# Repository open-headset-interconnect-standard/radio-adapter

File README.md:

# Open Source OHIS Radio Adapter(s?)
An open-source OHIS Radio Adapter.

As of 2024-07-17, this is a Work In Progress.

# Goals

1. Design a set of circuits that can be used to build OHIS compliant radio adapters.
2. Designs should be as simple as possible, but no simpler.
3. When laying out boards, keep as many parts through-hole as possible for ease of assembly.
4. There are two types of designs here:
    1. **General:** Has all the circuits required to work with any radio, that needs to be configured.
    2. **Radio Specific:** Trades Configurability for Simplicity.  Make a simpler device for a specific radio.

# Directory Structure

All KiCAD projects are in their own subdirectories off the git root.  Where it makes sense to do so, an additional layer of subdirectory may be used to group several projects together more obviously.

`/Documentation/` and `/docs/` are reserved for documentation source, and documentation output, respectively.

Everything in `/docs/` will be published on github Pages.

## Icom, Yaesu, Kenwood

As of 2024-04-04, I (@SmittyHalibut, Mark Smith, N6MTS) have submitted three schematics (only!) for VERY SIMPLE radio controllers for the Big Three.  A few notes about these:

* **I HAVE NOT TESTED THEM!**  There's no guaranty that they'll work, or even that they won't blow up your radio.  (It most likely won't blow up your radio. Probably.  I think.  It might.  It shouldn't.  Yeah, probably not.  But there's no telling.)
    * If you find a better way to do any of this, please submit a Pull Request, or at least an Issue with your idea.
* **YOU HAVE TO VERIFY PINOUTS MATCH YOUR RADIO!**  I've selected pinouts for most modern versions of these radios, but while researching this, it becomes obvious that older radios were not so consistent, even within a given manufacturer.  (Yaesu seems to be the worst at this, but they all do it.)
    * See [EB3GKE's Mic Pinout Reference](Yaesu/EB3GKE Mic Pinout Reference.pdf), it collects a lot of pinout information.  **BUT THEY GET RJ45 PINOUTS WRONG**.  As far as I could see, all (only most?) of their RJ45 pictures number pins 1 through 8 backwards.  OHIS's schematics are absolutely correct (verified against TIA-568 documents), so if the pinout for your radio looks VERY DIFFERENT than OHIS's pinouts, try reversing the pin numbers and see if thats closer.
* As of 2024-04-04, I've only done the schematics, and even then it's little more than throwing notes down "on paper."  I tried to cover:
    * Connector pinouts (see above).
    * Any electrical circuits required (mostly converting from OHIS's electret level to dynamic level for radios that want dynamic.)

As of 2024-04-25, I (still @SmittyHalibut) laid out the boards described above and had them fabricated.

* **I STILL HAVE NOT TESTED THEM!**

As of 2024-07-17, I (still me) am chatting with @gx1400 about this.  I'm going to send him some of the boards I ordered back in April and he'll help me test.

As of 2024-12-03, I (STILL me) am sending hardware to @gx1400 and a few others for testing.  These tests are covering:

* Yaesu:
  * :check: RJ45 8p8c
  * :check: RJ14 6p6c
  * :green_square: GX16
* Icom:
  * :green_square: RJ45 8p8c
  * :check: GX16
* Kenwood:
  * :check: RJ45 8p8c
  * :check: GX16

If you can test Yaesu GX16 or Icom RJ45, please reach out to me.  @SmittyHalibut on github, or on Discord.

# Parts

Electrical components, in recommended order of assembly:
* 1x 2x2 pin header right angle
* 1x 2x4 pin header right angle
* 1x 1k axial resistor
* 1x 6.2k axial resistor
* 2x 100R axial resistors
* 2x 10uF
* 1x 1k pot
* 1x 5381 (RJ45 with LED) for OHIS socket

Mechanical components, same as User kit:
* 4x M3 6mm screw
* 4x M3 10mm screw
* 4x M3 14mm brass stand-off
* 4x M3 3mm ABS stand-off
* 5x .1" jumper

PCBs in this repo:
* 2x Top-bottom panels
* 1x Main board
* 1x Shim board

Radio Specific parts, in recommended order of assembly:
* 1x Radio Specific Board
* 1x 3.5mm TRRS "headphone/speaker" connector
* Microphone connector.  Either one of:
  * 5380 (RJ45 with no LED) or 5381 (with LED) if its easier, but the LEDs aren't used.
  * GX16 connector, and GX16 riser board

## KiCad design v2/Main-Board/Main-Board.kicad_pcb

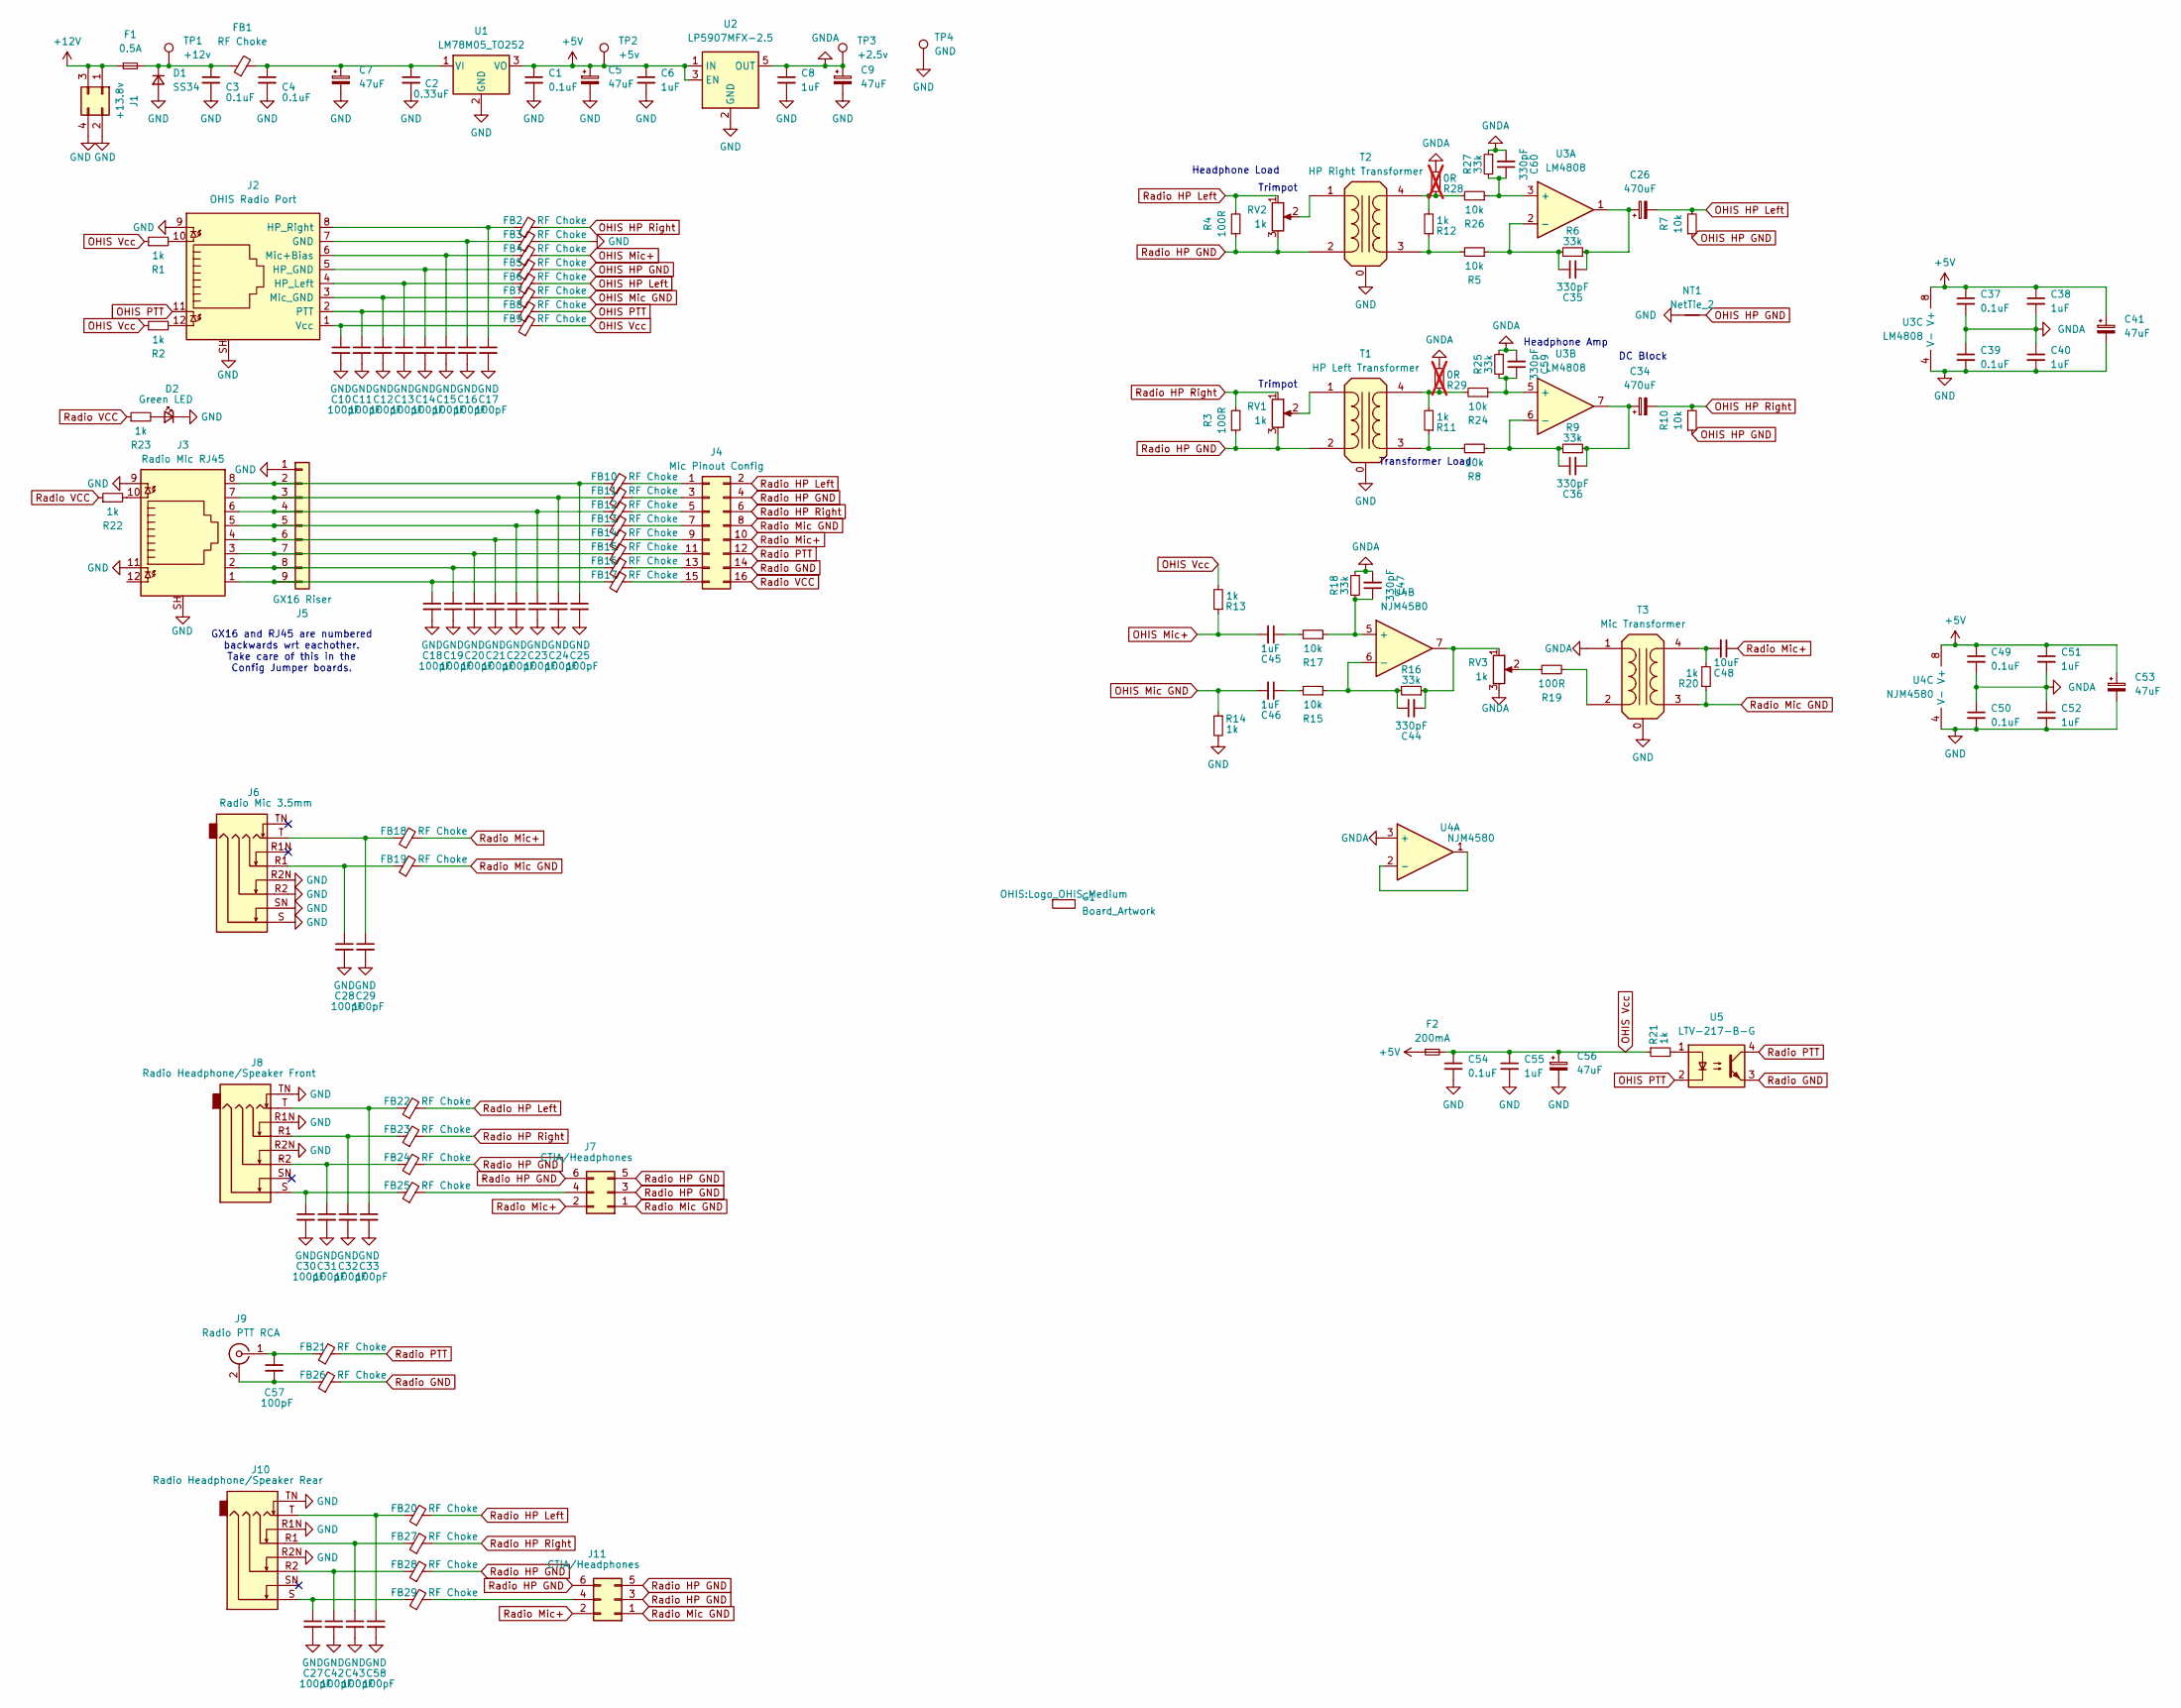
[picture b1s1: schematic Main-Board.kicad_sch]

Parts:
C1, C3, C4, C37, C39, C49, C50, C54: 0.1uF; C_0603_1608Metric; LCSC C14663
C2: 0.33uF; C_0603_1608Metric; LCSC C1615
C5, C9, C41, C53, C56: 47uF; C_0805_2012Metric; LCSC C16780
C6, C8, C38, C40, C45, C46, C51, C52, C55: 1uF; C_0603_1608Metric; LCSC C15849
C7: 47uF; CP_Elec_6.3x5.8; LCSC C401754
C10, C11, C12, C13, C14, C15, C16, C17, C18, C19, C20, C21, C22, C23, C24, C25, C27, C28, C29, C30, C31, C32, C33, C42, C43, C57, C58: 100pF; C_0603_1608Metric; LCSC C14858
C26, C34: 470uF; CP_Elec_6.3x7.7; LCSC C344072
C35, C36, C44, C47, C59, C60: 330pF; C_0603_1608Metric; LCSC C1664
C48: 10uF; C_0603_1608Metric; LCSC C19702
D1: SS34; D_SMA; LCSC C8678
D2: Green LED; LED_0805_2012Metric; LCSC C2297
F1: 0.5A; Fuse_1206_3216Metric; LCSC C720075
F2: 200mA; Fuse_0805_2012Metric; LCSC C516070
FB1, FB2, FB3, FB4, FB5, FB6, FB7, FB8, FB9, FB10, FB11, FB12, FB13, FB14, FB15, FB16, FB17, FB18, FB19, FB20, FB21, FB22, FB23, FB24, FB25, FB26, FB27, FB28, FB29: RF Choke; L_0805_2012Metric; LCSC C1017
G1: Board_Artwork; Logo_OHIS_Medium
J1: +13.8v; AndersonPP45-Dual
J2: OHIS Radio Port; Conn_RJ45_SMT_Amphenol-RJCSE-538X; LCSC C5384260
J3: Radio Mic RJ45; Conn_RJ45_SMT_Amphenol-RJCSE-538X; LCSC C5384260
J4: Mic Pinout Config; PinHeader_2x08_P2.54mm_Vertical_SMD; LCSC C32713288
J5: GX16 Riser; Conn_B2B-RA_2.54mm_9pin_Full-Slot
J6: Radio Mic 3.5mm; Conn_3.5mm-PJ-393-8_SMT-C668609; LCSC C668609
J7, J11: CTIA/Headphones; PinHeader_2x03_P2.54mm_Vertical_SMD; LCSC C32713283
J8: Radio Headphone/Speaker Front; Conn_3.5mm-PJ-393-8_SMT-C668609; LCSC C668609
J9: Radio PTT RCA; Conn_RCA_Kobiconn_156-009x-E
J10: Radio Headphone/Speaker Rear; Conn_3.5mm-PJ-393-8_SMT-C668609; LCSC C668609
NT1: NetTie_2; NetTie-2_SMD_Pad0.5mm
R1, R2, R11, R12, R13, R14, R20, R21, R22, R23: 1k; R_0603_1608Metric; LCSC C21190
R3, R4, R19: 100R; R_0603_1608Metric; LCSC C22775
R5, R7, R8, R10, R15, R17, R24, R26: 10k; R_0603_1608Metric; LCSC C25804
R6, R9, R16, R18, R25, R27: 33k; R_0603_1608Metric; LCSC C4216
R28, R29: 0R; R_0603_1608Metric; LCSC C21190; not fitted
RV1, RV2, RV3: 1k; Potentiometer_Bourns_3314J_Vertical; LCSC C124640
T1: HP Left Transformer; Transformer_ED8_4-Lead_10.5x8mm_P5mm; LCSC C840532
T2: HP Right Transformer; Transformer_ED8_4-Lead_10.5x8mm_P5mm; LCSC C840532
T3: Mic Transformer; Transformer_ED8_4-Lead_10.5x8mm_P5mm; LCSC C840532
TP1: +12v; TestPoint_THTPad_D1.5mm_Drill0.7mm
TP2: +5v; TestPoint_THTPad_D1.5mm_Drill0.7mm
TP3: +2.5v; TestPoint_THTPad_D1.5mm_Drill0.7mm
TP4: GND; TestPoint_THTPad_D1.5mm_Drill0.7mm
U1: LM78M05_TO252; TO-252-2; LCSC C58069
U2: LP5907MFX-2.5; SOT-23-5; LCSC C165132
U3: LM4808; SOP-8_3.76x4.96mm_P1.27mm; LCSC C910863
U4: NJM4580; SOP-8_3.76x4.96mm_P1.27mm; LCSC C3000516
U5: LTV-217-B-G; SO-4_4.4x2.3mm_P1.27mm; LCSC C115450

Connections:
+5V: C1.1, C5.1, C6.1, C37.1, C38.1, C41.1, C49.1, C51.1, C53.1, F2.1, TP2.1, U1.3 (VO), U2.1 (IN), U2.3 (EN), U3.8 (V+), U4.8 (V+)
+12V: F1.1, J1.1, J1.3
GND: C1.2, C2.2, C3.2, C4.2, C5.2, C6.2, C7.2, C8.2, C9.2, C10.2, C11.2, C12.2, C13.2, C14.2, C15.2, C16.2, C17.2, C18.2, C19.2, C20.2, C21.2, C22.2, C23.2, C24.2, C25.2, C27.2, C28.2, C29.2, C30.2, C31.2, C32.2, C33.2, C39.2, C40.2, C41.2, C42.2, C43.2, C50.2, C52.2, C53.2, C54.2, C55.2, C56.2, C58.2, D1.2 (A), D2.1 (K), FB3.2, J1.2, J1.4, J2.9, J2.SH, J3.9, J3.11, J3.SH, J5.1, J6.R2, J6.R2N, J6.S, J6.SN, J8.R1N, J8.R2N, J8.TN, J10.R1N, J10.R2N, J10.TN, NT1.1, R14.2, T1.0, T2.0, T3.0, TP4.1, U1.2 (GND), U2.2 (GND), U3.4 (V-), U4.4 (V-)
GNDA: C8.1, C9.1, C37.2, C38.2, C39.1, C40.1, C47.2, C49.2, C50.1, C51.2, C52.1, C59.2, C60.2, R18.1, R25.1, R27.1, R28.2, R29.2, RV3.3, T3.1 (AA), TP3.1, U2.5 (OUT), U4.3 (+)
unnamed: C26.1, C35.2, R6.1, U3.1
unnamed: C27.1, FB29.1, J10.S
unnamed: C28.1, FB19.1, J6.R1
unnamed: C29.1, FB18.1, J6.T
unnamed: C30.1, FB25.1, J8.S
unnamed: C31.1, FB24.1, J8.R2
unnamed: C32.1, FB23.1, J8.R1
unnamed: C33.1, FB22.1, J8.T
unnamed: C34.1, C36.2, R9.1, U3.7
unnamed: C42.1, FB28.1, J10.R2
unnamed: C43.1, FB27.1, J10.R1
unnamed: C44.2, R16.1, RV3.1, U4.7
unnamed: C45.1, R17.2
unnamed: C46.1, R15.2
unnamed: C58.1, FB20.1, J10.T
unnamed: C3.1, D1.1 (K), F1.2, FB1.1, TP1.1
unnamed: D2.2 (A), R23.2
unnamed: C16.1, FB3.1, J2.7 (GND)
unnamed: C14.1, FB5.1, J2.5 (HP_GND)
unnamed: C13.1, FB6.1, J2.4 (HP_Left)
unnamed: C17.1, FB2.1, J2.8 (HP_Right)
unnamed: C15.1, FB4.1, J2.6 (Mic+Bias)
unnamed: C12.1, FB7.1, J2.3 (Mic_GND)
unnamed: C11.1, FB8.1, J2.2 (PTT)
unnamed: J2.10, R1.2
unnamed: J2.12, R2.2
unnamed: C10.1, FB9.1, J2.1 (Vcc)
unnamed: J3.10, R22.2
unnamed: FB10.2, J4.1
unnamed: FB11.2, J4.3
unnamed: FB12.2, J4.5
unnamed: FB13.2, J4.7
unnamed: FB14.2, J4.9
unnamed: FB15.2, J4.11
unnamed: FB16.2, J4.13
unnamed: FB17.2, J4.15
unnamed: C25.1, FB10.1, J3.8, J5.2
unnamed: C24.1, FB11.1, J3.7, J5.3
unnamed: C23.1, FB12.1, J3.6, J5.4
unnamed: C22.1, FB13.1, J3.5, J5.5
unnamed: C21.1, FB14.1, J3.4, J5.6
unnamed: C20.1, FB15.1, J3.3, J5.7
unnamed: C19.1, FB16.1, J3.2, J5.8
unnamed: C18.1, FB17.1, J3.1, J5.9
unnamed: FB25.2, J7.4
unnamed: C57.2, FB26.1, J9.2 (Ext)
unnamed: C57.1, FB21.1, J9.1 (In)
unnamed: FB29.2, J11.4
unnamed: R19.1, RV3.2
unnamed: R21.2, U5.1
unnamed: RV1.2, T1.1 (AA)
unnamed: R8.2, R11.1, T1.3 (SA)
unnamed: R11.2, R24.2, R29.1, T1.4 (SB)
unnamed: RV2.2, T2.1 (AA)
unnamed: R5.2, R12.1, T2.3 (SA)
unnamed: R12.2, R26.2, R28.1, T2.4 (SB)
unnamed: R19.2, T3.2 (AB)
unnamed: C48.2, R20.2, T3.4 (SB)
unnamed: C2.1, C4.1, C7.1, FB1.2, U1.1 (VI)
unnamed: C60.1, R26.1, R27.2, U3.3 (+)
unnamed: C35.1, R5.1, R6.2, U3.2 (-)
unnamed: C59.1, R24.1, R25.2, U3.5 (+)
unnamed: C36.1, R8.1, R9.2, U3.6 (-)
unnamed: U4.1, U4.2 (-)
unnamed: C47.1, R17.1, R18.2, U4.5 (+)
unnamed: C44.1, R15.1, R16.2, U4.6 (-)
OHIS HP GND: FB5.2, NT1.2, R7.1, R10.1
OHIS HP Left: C26.2, FB6.2, R7.2
OHIS HP Right: C34.2, FB2.2, R10.2
OHIS Mic GND: C46.2, FB7.2, R14.1
OHIS Mic+: C45.2, FB4.2, R13.1
OHIS PTT: FB8.2, J2.11, U5.2
OHIS Vcc: C54.1, C55.1, C56.1, F2.2, FB9.2, R1.1, R2.1, R13.2, R21.1
Radio GND: FB26.2, J4.14, U5.3
Radio HP GND: FB24.2, FB28.2, J4.4, J7.3, J7.5, J7.6, J11.3, J11.5, J11.6, R3.1, R4.1, RV1.3, RV2.3, T1.2 (AB), T2.2 (AB)
Radio HP Left: FB20.2, FB22.2, J4.2, R4.2, RV2.1
Radio HP Right: FB23.2, FB27.2, J4.6, R3.2, RV1.1
Radio Mic GND: FB19.2, J4.8, J7.1, J11.1, R20.1, T3.3 (SA)
Radio Mic+: C48.1, FB18.2, J4.10, J7.2, J11.2
Radio PTT: FB21.2, J4.12, U5.4
Radio VCC: J4.16, R22.1, R23.1

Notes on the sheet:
Trimpot
Headphone Load
Headphone Amp
DC Block
GX16 and RJ45 are numbered backwards wrt eachother. Take care of this in the Config Jumper boards.
Transformer Load

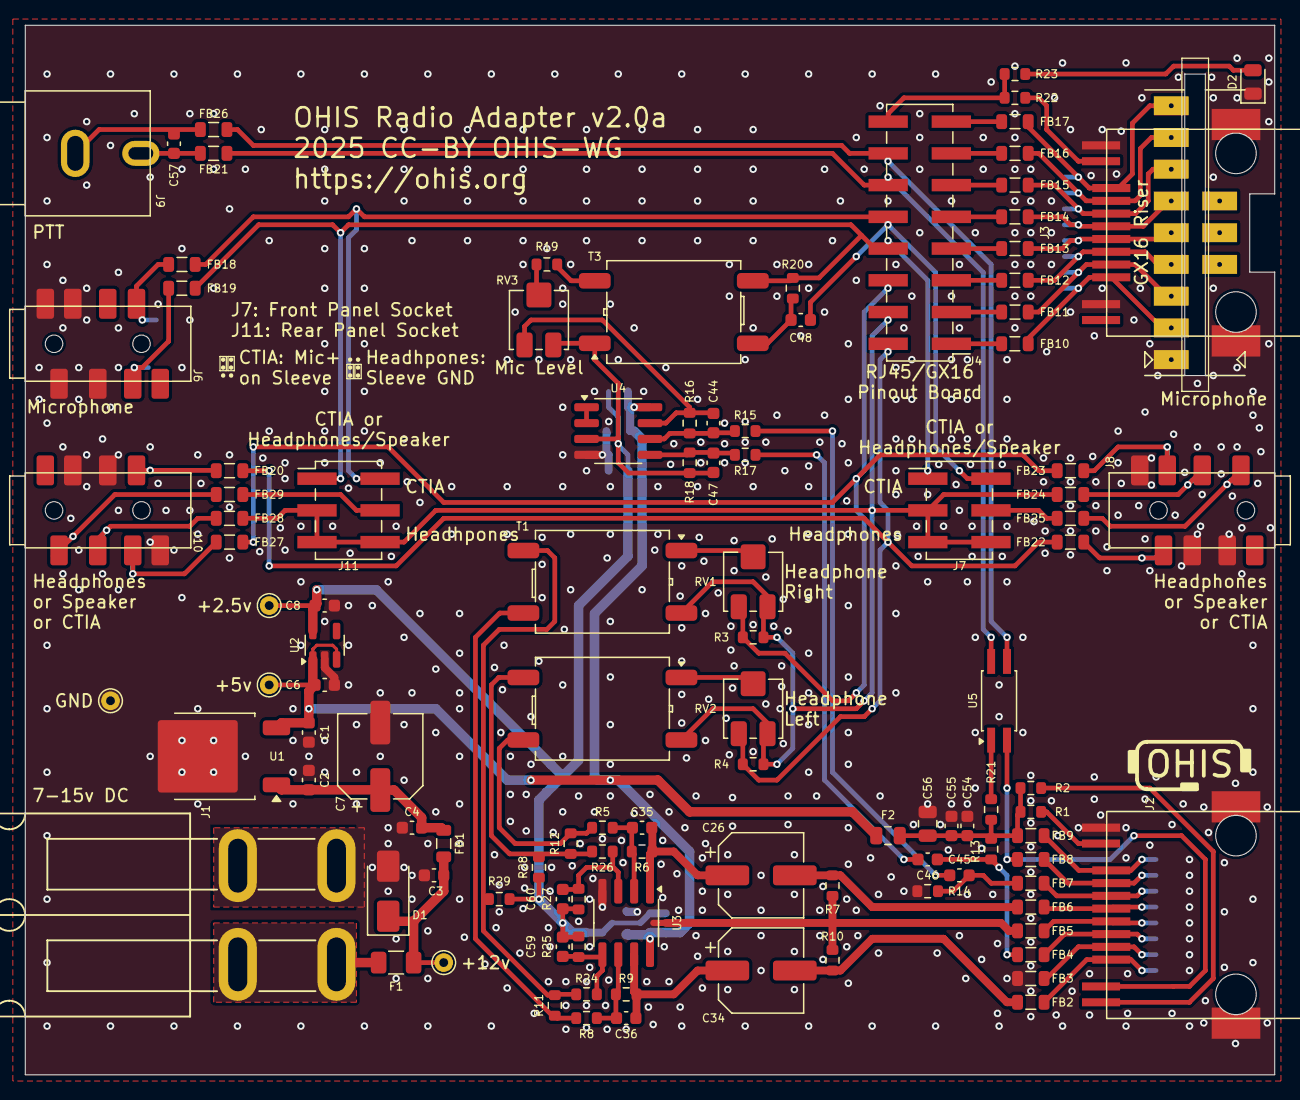
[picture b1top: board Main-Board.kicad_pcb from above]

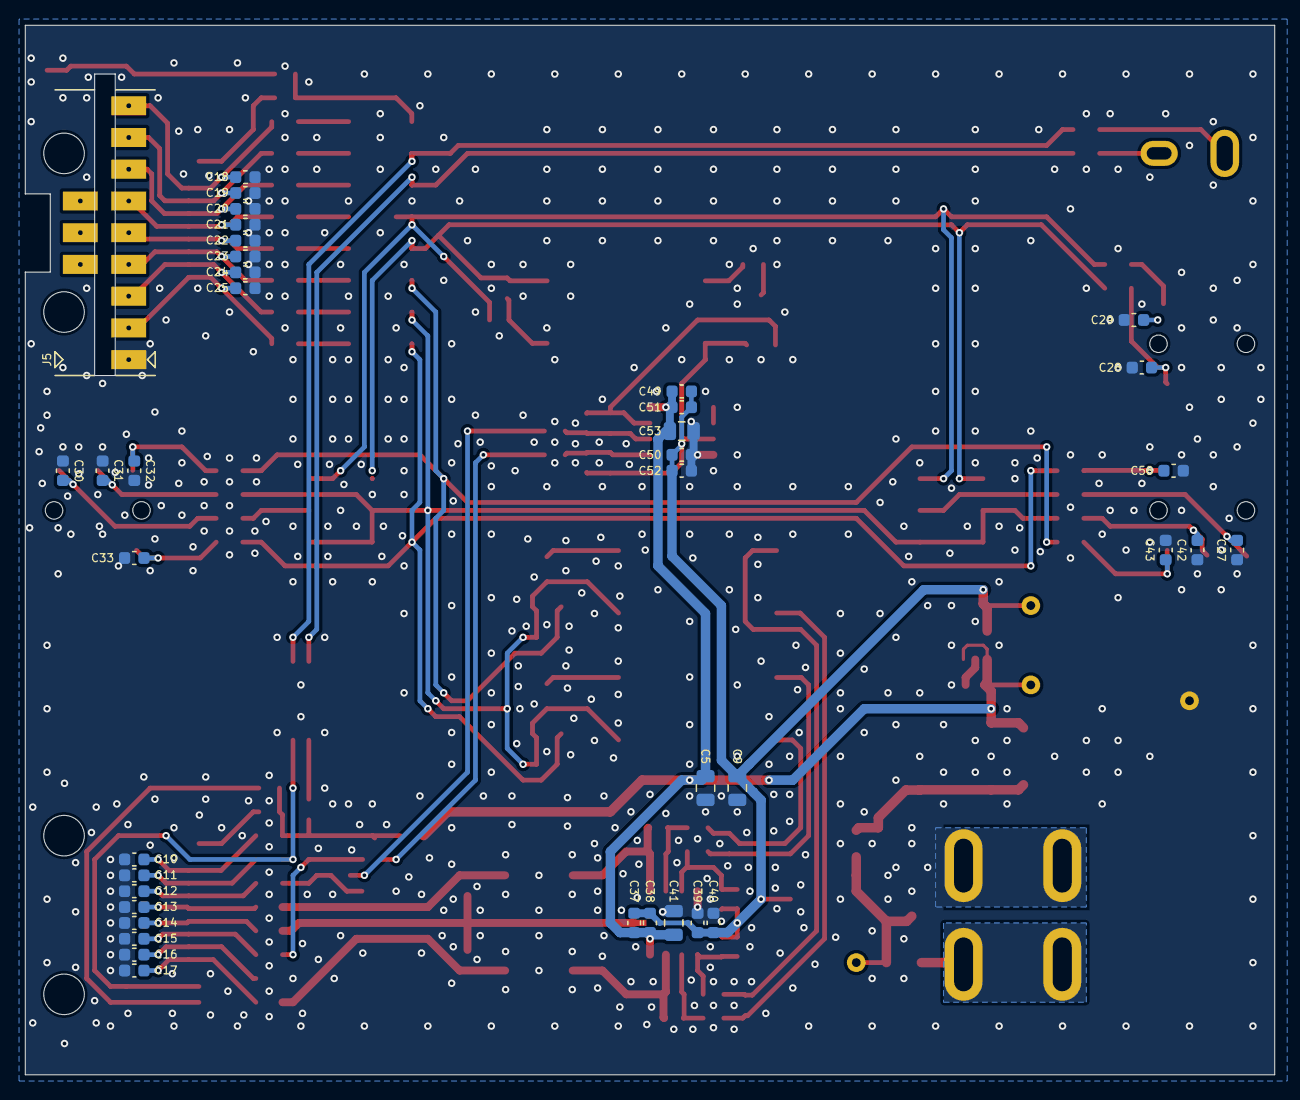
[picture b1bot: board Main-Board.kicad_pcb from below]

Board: 2 copper layers, 100.0 x 84.0 mm, 150 parts (39 on the bottom side), 85 nets.

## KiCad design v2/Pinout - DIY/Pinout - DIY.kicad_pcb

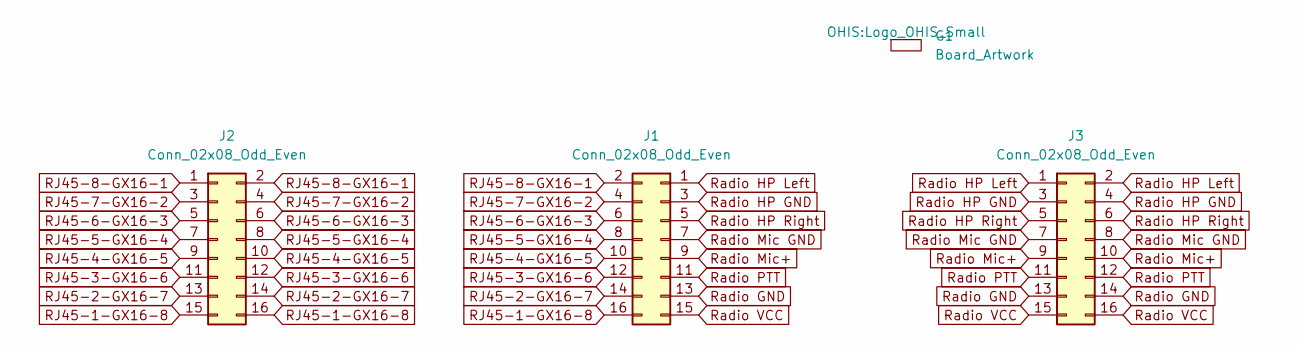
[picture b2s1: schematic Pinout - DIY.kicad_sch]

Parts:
G1: Board_Artwork; Logo_OHIS_Small
J1, J2, J3: Conn_02x08_Odd_Even; PinSocket_2x08_P2.54mm_Vertical

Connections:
RJ45-1-GX16-8: J1.16, J2.15, J2.16
RJ45-2-GX16-7: J1.14, J2.13, J2.14
RJ45-3-GX16-6: J1.12, J2.11, J2.12
RJ45-4-GX16-5: J1.10, J2.9, J2.10
RJ45-5-GX16-4: J1.8, J2.7, J2.8
RJ45-6-GX16-3: J1.6, J2.5, J2.6
RJ45-7-GX16-2: J1.4, J2.3, J2.4
RJ45-8-GX16-1: J1.2, J2.1, J2.2
Radio GND: J1.13, J3.13, J3.14
Radio HP GND: J1.3, J3.3, J3.4
Radio HP Left: J1.1, J3.1, J3.2
Radio HP Right: J1.5, J3.5, J3.6
Radio Mic GND: J1.7, J3.7, J3.8
Radio Mic+: J1.9, J3.9, J3.10
Radio PTT: J1.11, J3.11, J3.12
Radio VCC: J1.15, J3.15, J3.16

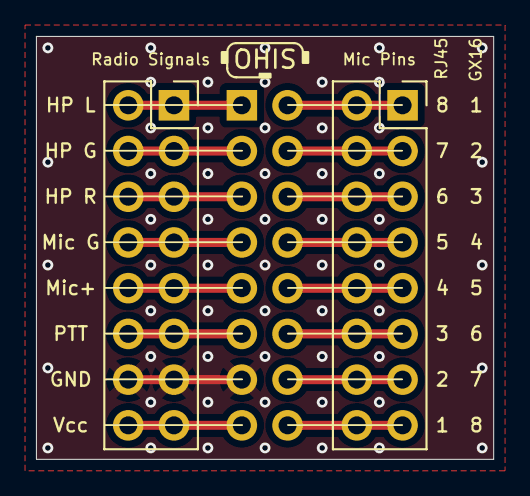
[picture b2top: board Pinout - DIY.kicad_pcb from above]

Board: 2 copper layers, 25.4 x 23.5 mm, 4 parts (1 on the bottom side), 16 nets.

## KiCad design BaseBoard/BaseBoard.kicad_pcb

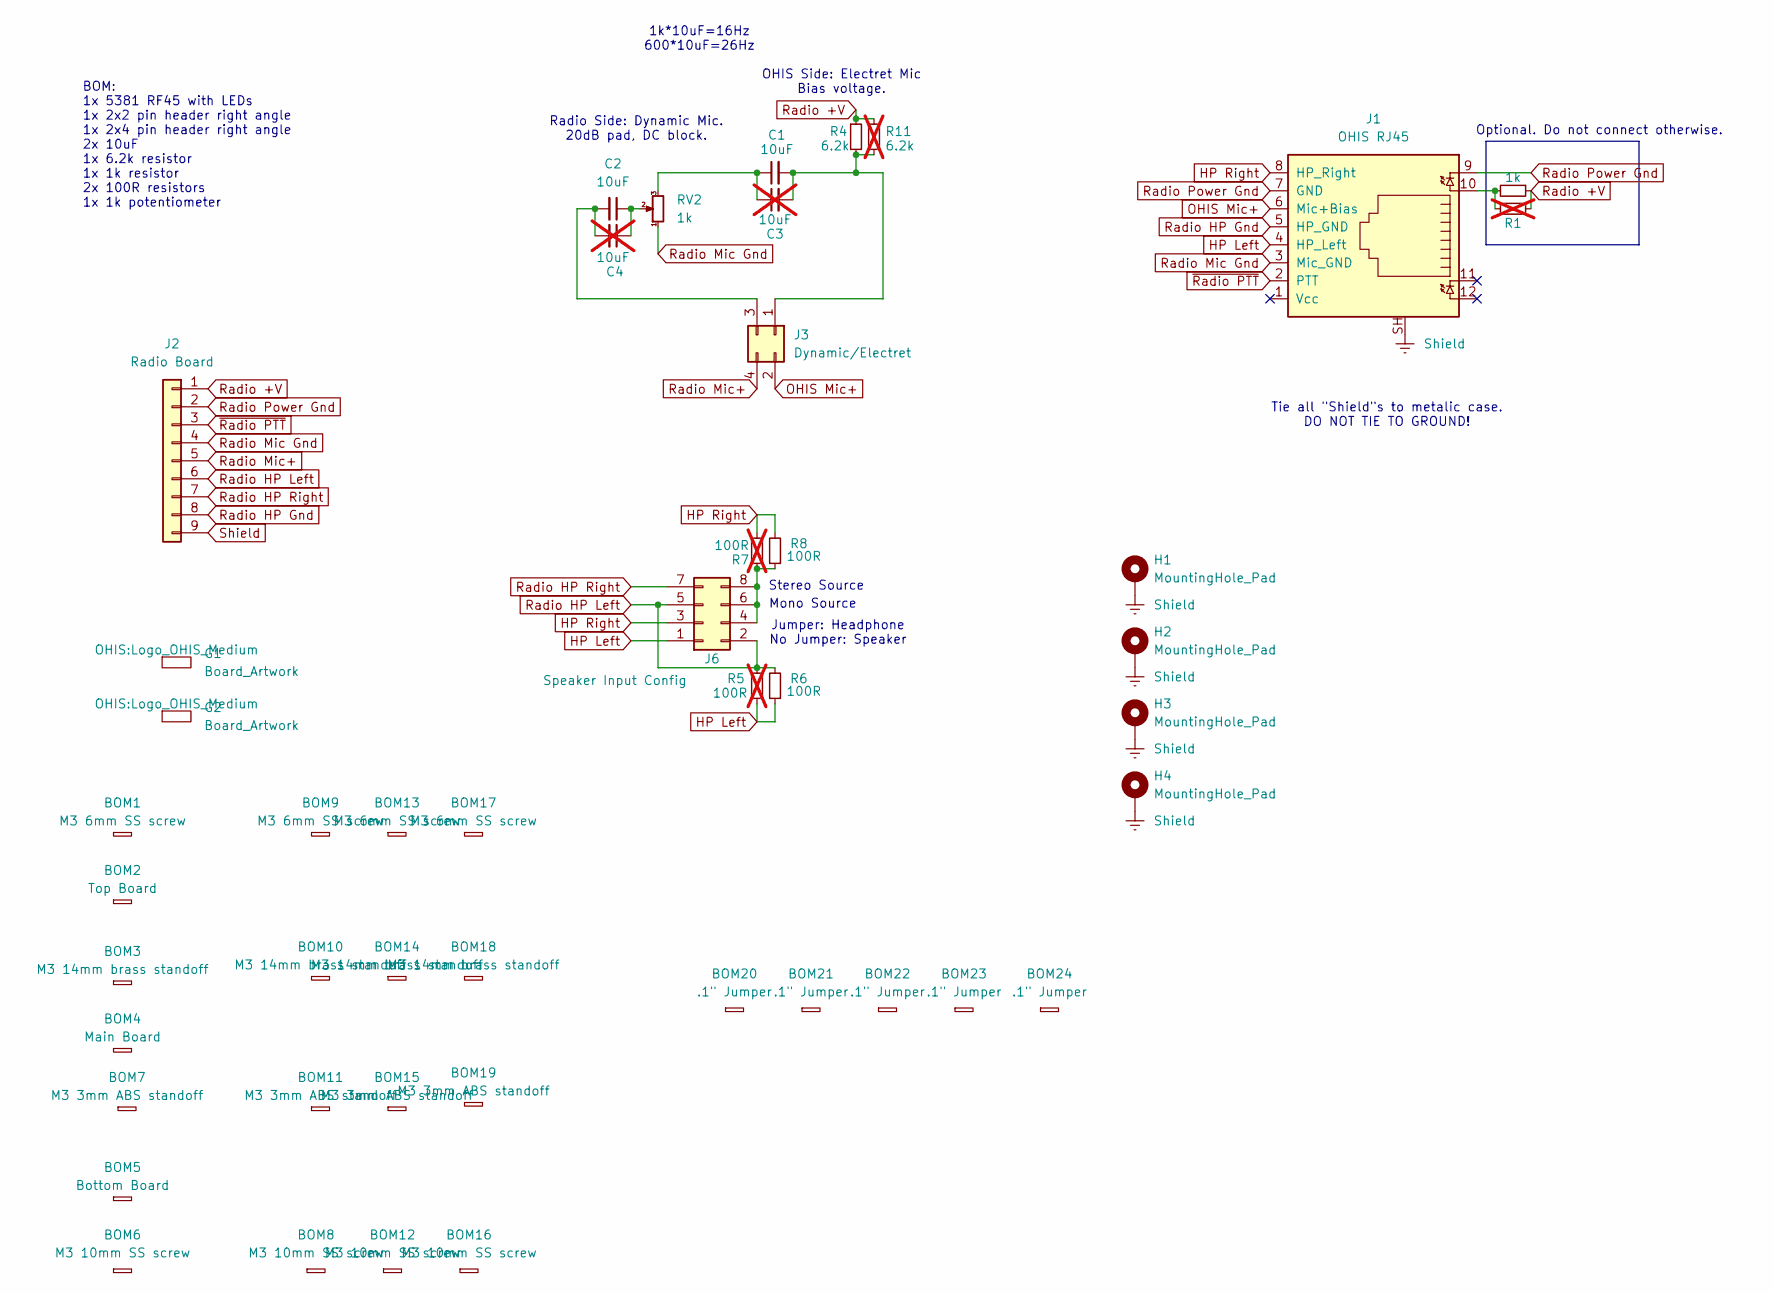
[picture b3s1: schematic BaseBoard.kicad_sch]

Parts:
BOM1, BOM9, BOM13, BOM17: M3 6mm SS screw; BOM_Item; Part Number M3 6mm SS screw
BOM2: Top Board; BOM_Item
BOM3, BOM10, BOM14, BOM18: M3 14mm brass standoff; BOM_Item; Part Number M3 14mm brass standoff
BOM4: Main Board; BOM_Item
BOM5: Bottom Board; BOM_Item
BOM6, BOM8, BOM12, BOM16: M3 10mm SS screw; BOM_Item; Part Number M3 10mm SS screw
BOM7, BOM11, BOM15, BOM19: M3 3mm ABS standoff; BOM_Item; Part Number M3 3mm ABS standoff
BOM20, BOM21, BOM22, BOM23, BOM24: .1" Jumper; BOM_Item; Part Number .1" Pin Jumper
C1, C2: 10uF; C_Disc_D4.7mm_W2.5mm_P5.00mm; Part Number FG28X5R1E106MRT06
C3, C4: 10uF; C_1206_3216Metric; not fitted
G1, G2: Board_Artwork; Logo_OHIS_Medium
H1, H2, H3, H4: MountingHole_Pad; MountingHole_3.2mm_M3_Pad
J1: OHIS RJ45; RJ45_Amphenol_RJHSE538X; Part Number RJHSE-5381
J2: Radio Board; Conn_B2B-RA_2.54mm_9pin_LtoR
J3: Dynamic/Electret; PinHeader_2x02_P2.54mm_Horizontal; Part Number .1" 3x40 right angle 2.54mm Pin Header
J6: Speaker Input Config; PinHeader_2x04_P2.54mm_Horizontal; Part Number .1" 3x40 right angle 2.54mm Pin Header; LCSC C9139
R1: 1k; R_Axial_DIN0207_L6.3mm_D2.5mm_P7.62mm_Horizontal; Part Number CFR-12JB-52-1K
R4: 6.2k; R_Axial_DIN0207_L6.3mm_D2.5mm_P7.62mm_Horizontal; Part Number CFR-12JB-52-6K2
R5, R7: 100R; R_1206_3216Metric; not fitted
R6, R8: 100R; R_Axial_DIN0207_L6.3mm_D2.5mm_P7.62mm_Horizontal; Part Number CFR-12JB-52-100R
R11: 6.2k; R_1206_3216Metric; not fitted
R12: 1k; R_1206_3216Metric; not fitted
RV2: 1k; Potentiometer_Piher_PT-6-H_Horizontal; Part Number N6-S25T0C-102

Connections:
HP Left: J1.4 (HP_Left), J6.1, R5.1, R6.1
HP Right: J1.8 (HP_Right), J6.3, R7.1, R8.2
unnamed: C1.1, C3.1, RV2.3
unnamed: C2.1, C4.1, RV2.2
unnamed: J1.10, R1.2, R12.2
unnamed: C1.2, C3.2, J3.1, R4.2, R11.2
unnamed: C2.2, C4.2, J3.3
unnamed: J6.4, J6.6, J6.8, R7.2, R8.1
OHIS Mic+: J1.6 (Mic+Bias), J3.2
Radio +V: J2.1, R1.1, R4.1, R11.1, R12.1
Radio HP Gnd: J1.5 (HP_GND), J2.8
Radio HP Left: J2.6, J6.2, J6.5, R5.2, R6.2
Radio HP Right: J2.7, J6.7
Radio Mic Gnd: J1.3 (Mic_GND), J2.4, RV2.1
Radio Mic+: J2.5, J3.4
Radio Power Gnd: J1.7 (GND), J1.9, J2.2
Shield: H1.1, H2.1, H3.1, H4.1, J1.SH, J2.9
~Radio PTT: J1.2 (PTT), J2.3

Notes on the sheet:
Stereo Source
OHIS Side: Electret Mic Bias voltage.
Mono Source
Radio Side: Dynamic Mic. 20dB pad, DC block.
Tie all "Shield"s to metalic case. DO NOT TIE TO GROUND!
1k*10uF=16Hz 600*10uF=26Hz
BOM: 1x 5381 RF45 with LEDs 1x 2x2 pin header right angle 1x 2x4 pin header right angle 2x 10uF 1x 6.2k resistor 1x 1k resistor 2x 100R resistors 1x 1k potentiometer
Jumper: Headphone No Jumper: Speaker
Optional. Do not connect otherwise.

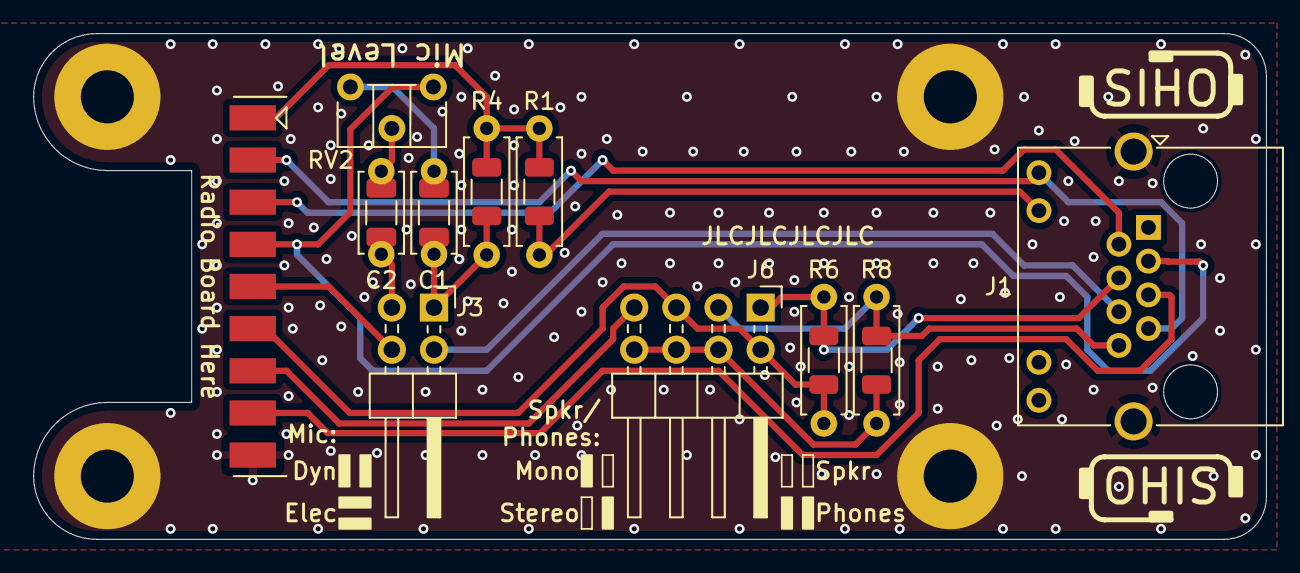
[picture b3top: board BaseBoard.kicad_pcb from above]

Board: 2 copper layers, 74.3 x 30.5 mm, 47 parts (0 on the bottom side), 18 nets.

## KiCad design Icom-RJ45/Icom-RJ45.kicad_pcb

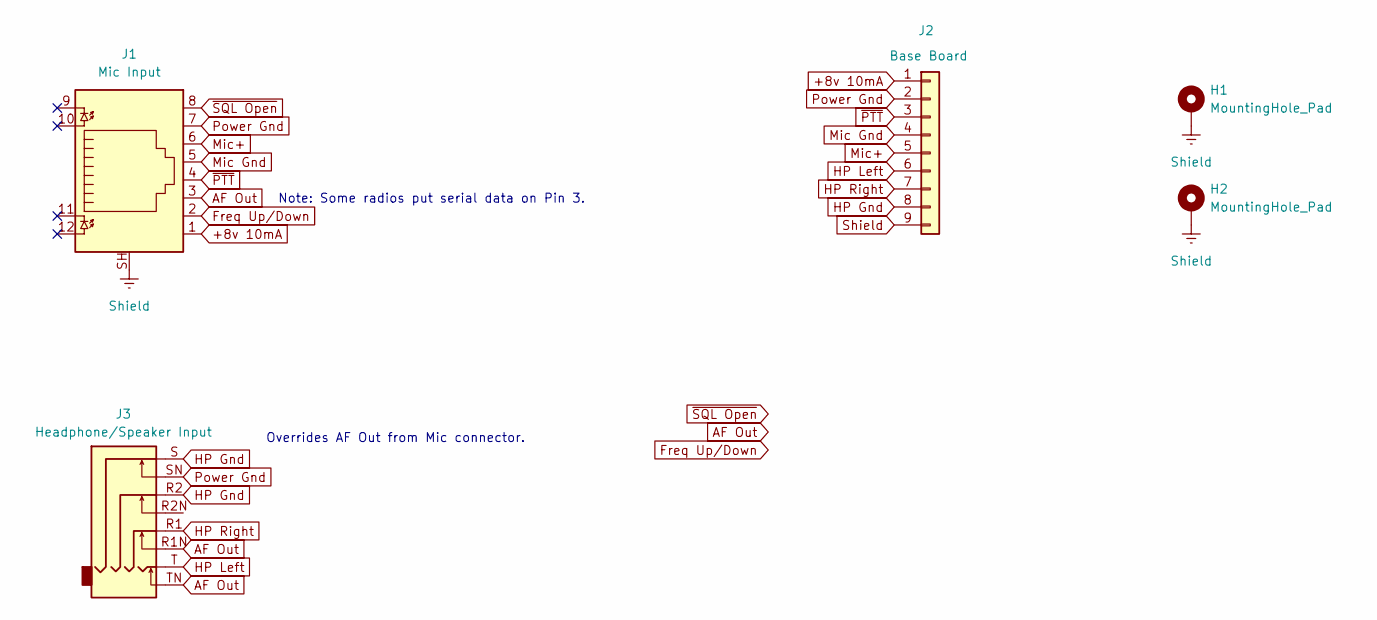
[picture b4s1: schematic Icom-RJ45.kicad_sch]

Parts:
H1, H2: MountingHole_Pad; MountingHole_3.2mm_M3_Pad
J1: Mic Input; RJ45_Amphenol_RJHSE538X
J2: Base Board; Conn_B2B-RA_2.54mm_9pin_RtoL
J3: Headphone/Speaker Input; Conn_3.5mm-PJ-393_SMT-C668609_TH-C145811

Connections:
+8v 10mA: J1.1, J2.1
AF Out: J1.3, J3.R1N, J3.TN
Freq Up/Down: J1.2
HP Gnd: J2.8, J3.R2, J3.S
HP Left: J2.6, J3.T
HP Right: J2.7, J3.R1
Mic Gnd: J1.5, J2.4
Mic+: J1.6, J2.5
Power Gnd: J1.7, J2.2, J3.SN
Shield: H1.1, H2.1, J1.SH, J2.9
~PTT: J1.4, J2.3
~SQL Open: J1.8

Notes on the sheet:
Note: Some radios put serial data on Pin 3.
Overrides AF Out from Mic connector.

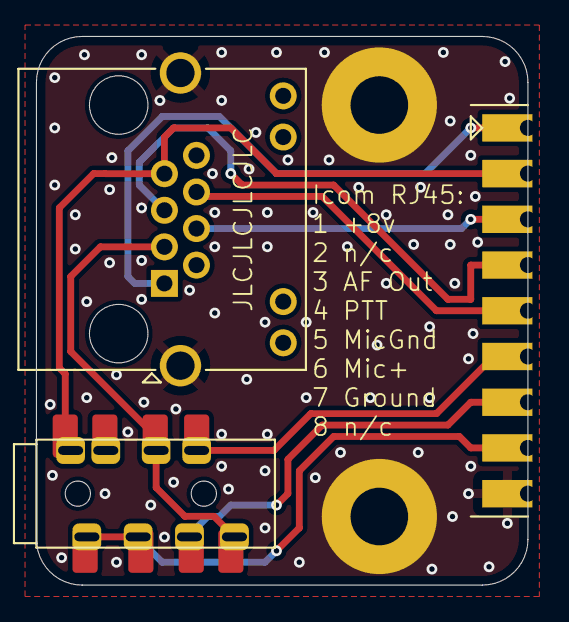
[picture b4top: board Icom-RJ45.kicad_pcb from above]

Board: 2 copper layers, 27.3 x 30.5 mm, 6 parts (1 on the bottom side), 10 nets.

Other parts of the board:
G1: Logo_OHIS; Logo_OHIS_Medium

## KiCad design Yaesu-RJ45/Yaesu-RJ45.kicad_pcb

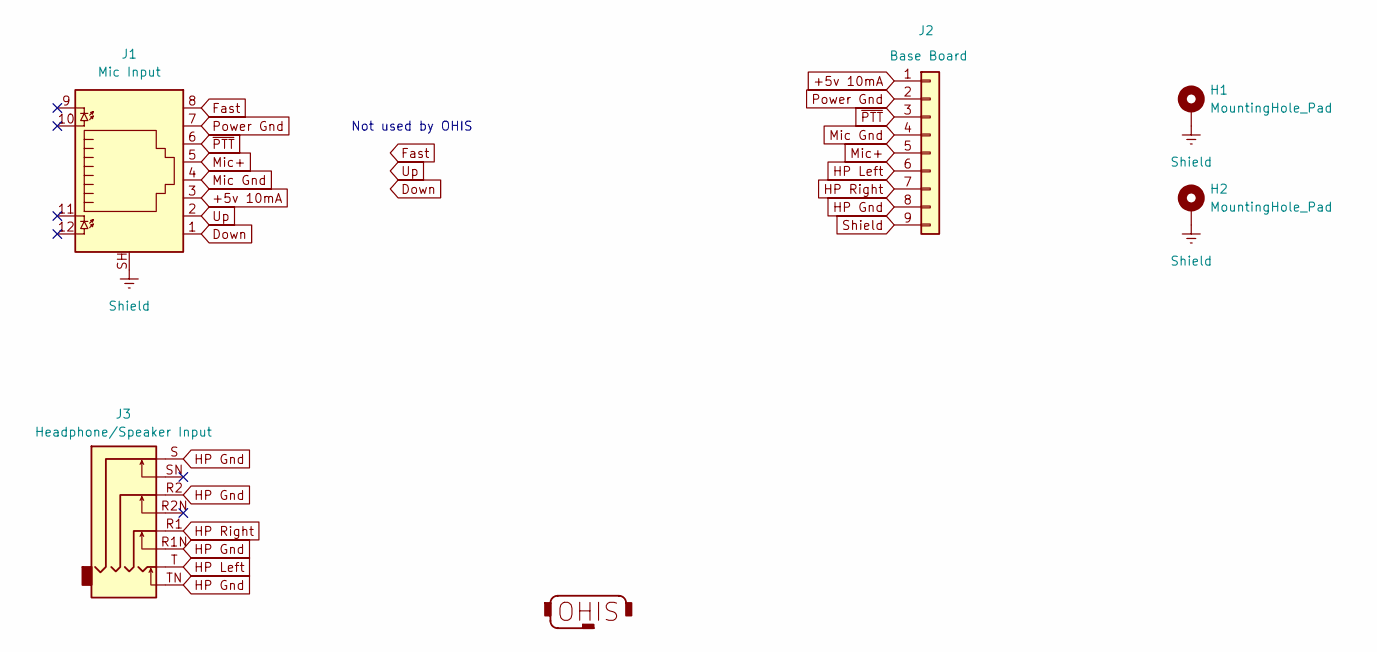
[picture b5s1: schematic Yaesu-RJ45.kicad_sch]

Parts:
G1: Logo_OHIS; Logo_OHIS_Medium
H1, H2: MountingHole_Pad; MountingHole_3.2mm_M3_Pad
J1: Mic Input; RJ45_Amphenol_RJHSE538X
J2: Base Board; Conn_B2B-RA_2.54mm_Castelated_9pin_RtoL
J3: Headphone/Speaker Input; Conn_3.5mm-PJ-393_SMT-C668609_TH-C145811

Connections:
+5v 10mA: J1.3, J2.1
Down: J1.1
Fast: J1.8
HP Gnd: J2.8, J3.R1N, J3.R2, J3.S, J3.TN
HP Left: J2.6, J3.T
HP Right: J2.7, J3.R1
Mic Gnd: J1.4, J2.4
Mic+: J1.5, J2.5
Power Gnd: J1.7, J2.2
Shield: H1.1, H2.1, J1.SH, J2.9
Up: J1.2
~PTT: J1.6, J2.3

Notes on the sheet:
Not used by OHIS

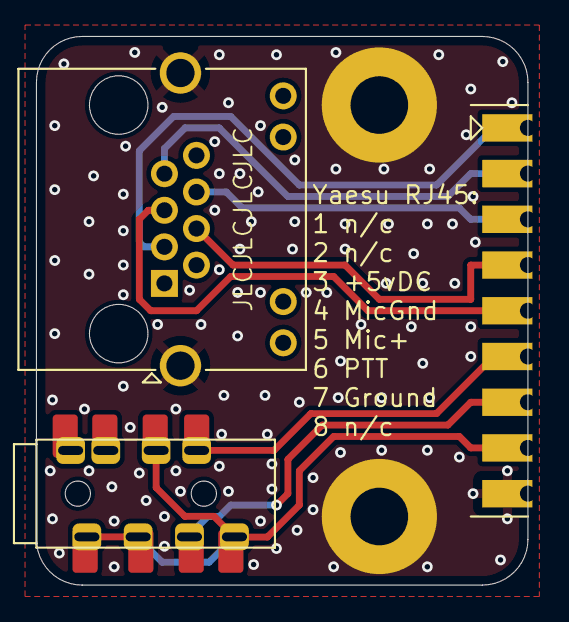
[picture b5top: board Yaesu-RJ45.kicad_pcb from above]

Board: 2 copper layers, 27.3 x 30.5 mm, 6 parts (1 on the bottom side), 9 nets.

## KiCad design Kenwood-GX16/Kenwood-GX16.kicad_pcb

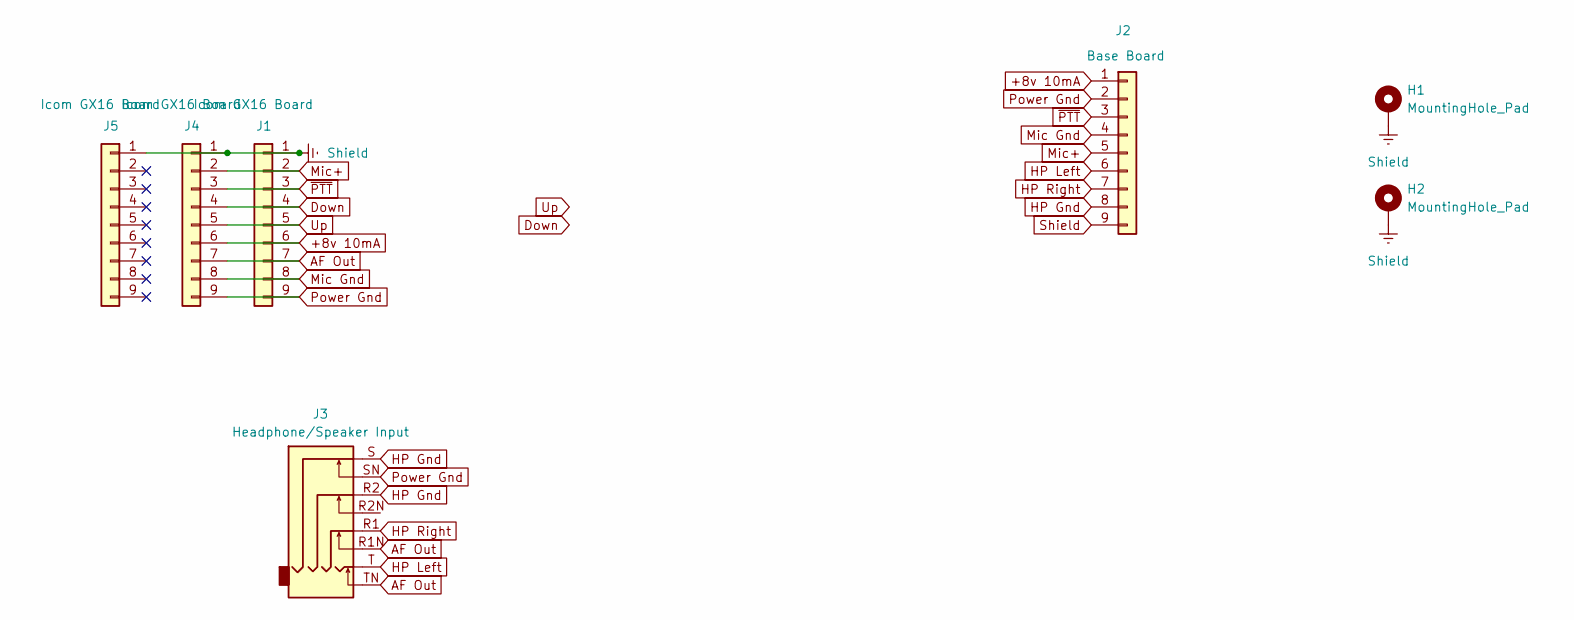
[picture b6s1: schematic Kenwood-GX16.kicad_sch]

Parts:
H1, H2: MountingHole_Pad; MountingHole_3.2mm_M3_Pad
J1: Icom GX16 Board; Conn_B2B-RA_2.54mm_9pin_RtoL
J2: Base Board; Conn_B2B-RA_2.54mm_Castelated_9pin_RtoL
J3: Headphone/Speaker Input; Conn_3.5mm-PJ-393_SMT-C668609_TH-C145811
J4, J5: Icom GX16 Board; Conn_B2B-RA_2.54mm_9pin_LtoR

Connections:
+8v 10mA: J1.6, J2.1, J4.6
AF Out: J1.7, J3.R1N, J3.TN, J4.7
Down: J1.4, J4.4
HP Gnd: J2.8, J3.R2, J3.S
HP Left: J2.6, J3.T
HP Right: J2.7, J3.R1
Mic Gnd: J1.8, J2.4, J4.8
Mic+: J1.2, J2.5, J4.2
Power Gnd: J1.9, J2.2, J3.SN, J4.9
Shield: H1.1, H2.1, J1.1, J2.9, J4.1, J5.1
Up: J1.5, J4.5
~PTT: J1.3, J2.3, J4.3

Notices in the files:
BaseBoard/BaseBoard.kicad_pcb:
2024 CC-BY OHIS-WG ohis.org
v2/Main-Board/Main-Board.kicad_pcb:
2025 CC-BY OHIS-WG
